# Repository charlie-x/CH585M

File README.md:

# CH585M
CH585M altium conversion to eagle

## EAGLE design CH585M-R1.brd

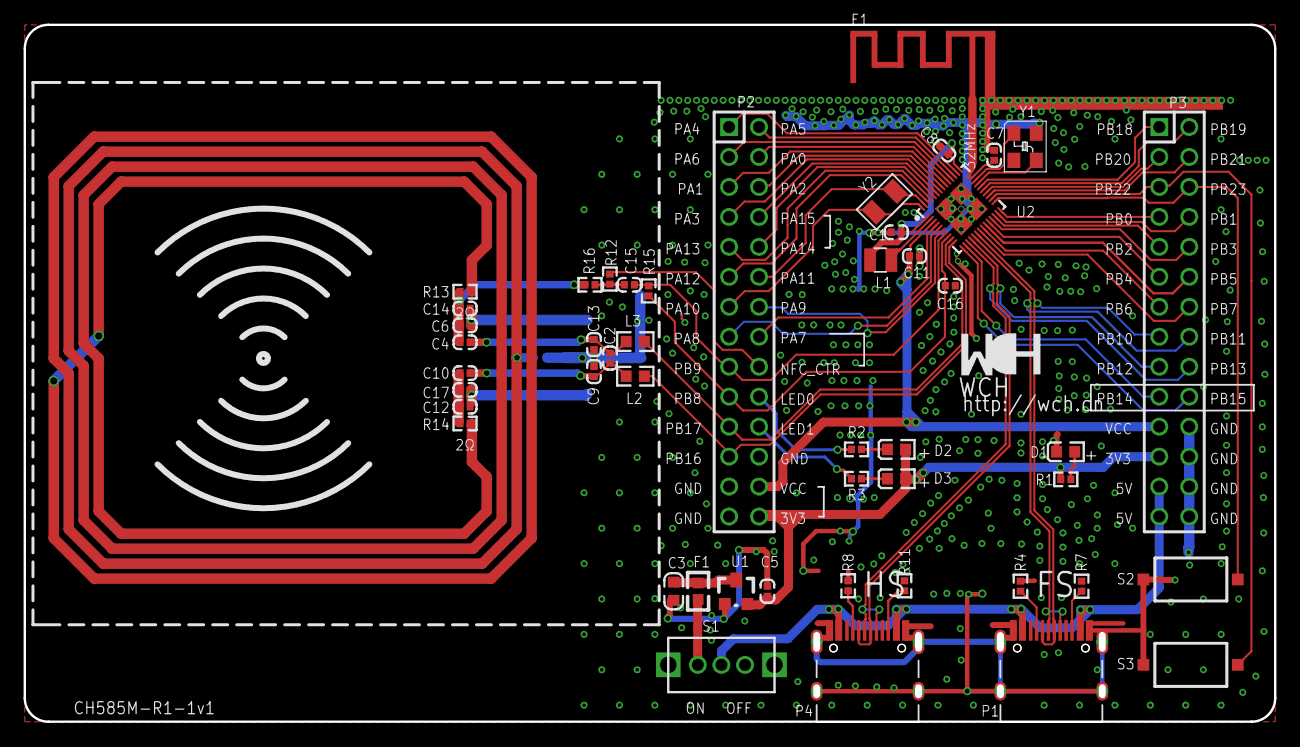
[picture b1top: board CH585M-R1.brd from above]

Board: 2 copper layers, 106.0 x 59.1 mm, 49 parts (1 on the bottom side), 68 nets.

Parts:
C1: 4.7uF; 0402_C_8B34AB
C2: NC; 0402_C
C3: 10uF; 0603_C
C4, C10: 30pF 2%; 0402_C_A5B067
C5: 2.2uF; 0402_C
C6: NC; 0402_C_A5B067
C7: 0.47uF; 0402_C
C8: 0.1uF; 0402_C_EA6F3D
C9, C13: 100pF 2%; 0402_C
C11: 2.2uF; 0402_C_A5B067
C12: 200pf 2%; 0402_C_8B34AB
C14: 200pf 2%; 0402_C_A5B067
C15: 10nF; 0402_C_A5B067
C16: 10nF; 0402_C_8B34AB
C17: NC; 0402_C_8B34AB
D1: POWER; 0603+
D2: LED0; 0603+
D3: LED1; 0603+
E1: ANTENNA; ANT-F-1-2.4G-1.6MMFR4
F1: 500mA; 0603_8BD959
L1: 10uH; SMD_2X2MM
L2, L3: 1uH; 0603
P1: TYPE-C FS-USB; TYPE-C-RECEPTACLE-2.0
P2, P3: HEADER 14x2; IDC28-2.54MM
P4: TYPE-C HS-USB; TYPE-C-RECEPTACLE-2.0
R1, R2, R3: 1K; 0402_B3DFE5
R4, R7, R8, R11: 5.1K; 0402_B3DFE5
R12: 1kΩ; 0402_B3DFE5
R13, R14: 1Ω(4.7Ω); 0402_B3DFE5
R15: NC; 0402_B3DFE5
R16: 2kΩ; 0402_B3DFE5
R17: NC; 0402
S1: SW; SW1
S2: RST#; SMD_6.1X3.65X2.5MM-KEY
S3: Download; SMD_6.1X3.65X2.5MM-KEY
U1: 6219P33M; SOT-23
U2: CH585M; QFN48_5X5
Y1: 32MHz ±10ppm 12pF 30Ω; XT3225
Y2: 32.768K; FC-135

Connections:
+3V3: C5.1, D2.1, D3.1, P2.28, P3.23, R1.2, U1.2
+5V: P1.A4, P1.B4, P3.25, P3.27, P4.A4, P4.B4, S1.1
ANT: E1.1, U2.34
BOOT: P3.5, S3.2, U2.26
GND: C1.1, C3.2, C5.2, C6.1, C7.2, C8.2, C9.2, C11.1, C12.2, C13.1, C14.1, C16.2, C17.2, D1.2, E1.0, P1.0, P1.0B, P1.0T, P1.0_2, P1.0_2B, P1.0_2T, P1.0_3, P1.0_3B, P1.0_3T, P1.0_4, P1.0_4B, P1.0_4T, P1.A1, P1.B1, P2.24, P2.25, P2.27, P3.22, P3.24, P3.26, P3.28, P4.0, P4.0B, P4.0T, P4.0_2, P4.0_2B, P4.0_2T, P4.0_3, P4.0_3B, P4.0_3T, P4.0_4, P4.0_4B, P4.0_4T, P4.A1, P4.B1, R4.1, R7.2, R8.1, R11.2, R17.2, S2.1, S3.1, U1.1, U2.0, U2.0_2, U2.0_3, U2.0_4, U2.0_5, U2.0_6, U2.0_7, U2.0_8, U2.0_9, Y1.2, Y1.4
LED0: P2.20, R2.1
LED1: P2.22, R3.1
NETC2_1: C2.1, C9.1, C10.1, L2.2
NETC2_2: C2.2, C4.1, C13.2, L3.2
NETC4_2: C4.2, C6.2, C14.2, R13.1, R16.1
NETC10_2: C10.2, C12.1, C17.1, R14.1
NETC15_2: C15.2, R12.1, R16.2
NETD1_1: D1.1, R1.1
NETD2_2: D2.2, R2.2
NETD3_2: D3.2, R3.2
NETF1_1: F1.1, S1.2
NETP1_A5: P1.A5, R4.2
NETP1_B5: P1.B5, R7.1
NETP4_A5: P4.A5, R8.2
NETP4_B5: P4.B5, R11.1
NETR13_2: R13.2, R14.2, R17.1
NFC+: L3.1, P2.21, U2.9
NFC-: L2.1, P2.23, U2.10
NFCI: C15.1, P2.17, R15.1, U2.7
NFCM: C16.1, P2.19, R15.2, U2.8
NFC_CTR: P2.18, R12.2
PA0: P2.4, U2.39
PA1: P2.5, U2.40
PA2: P2.6, U2.41
PA3: P2.7, U2.42
PA4: P2.1, U2.36
PA5: P2.2, U2.37
PA6: P2.3, U2.38
PA7: P2.16, U2.4
PA8: P2.15, U2.5
PA9: P2.14, U2.6
PA10: P2.13, U2.48, Y2.1
PA11: P2.12, U2.47, Y2.2
PA12: P2.11, U2.46
PA13: P2.9, U2.45
PA14: P2.10, U2.44
PA15: P2.8, U2.43
PB0: P3.7, U2.24
PB1: P3.8, U2.23
PB2: P3.9, U2.22
PB3: P3.10, U2.21
PB4: P3.11, U2.20
PB5: P3.12, U2.19
PB6: P3.13, U2.18
PB7: P3.14, U2.17
PB10: P1.A7, P1.B7, P3.15, U2.16
PB11: P1.A6, P1.B6, P3.16, U2.15
PB12: P3.17, P4.A7, P4.B7, U2.14
PB13: P3.18, P4.A6, P4.B6, U2.13
PB14: P3.19, U2.12
PB15: P3.20, U2.11
PB18: P3.1, U2.30
PB19: P3.2, U2.29
PB20: P3.3, U2.28
PB21: P3.4, U2.27
PB23: P3.6, S2.2, U2.25
V5V: C3.1, F1.2, U1.3
VCC: C11.2, P2.26, P3.21, U2.3
VDCIA: C1.2, C8.1, L1.2, U2.1, U2.35
VINTA: C7.1, U2.33
VSW: L1.1, U2.2
X32MI: U2.32, Y1.1
X32MO: U2.31, Y1.3
